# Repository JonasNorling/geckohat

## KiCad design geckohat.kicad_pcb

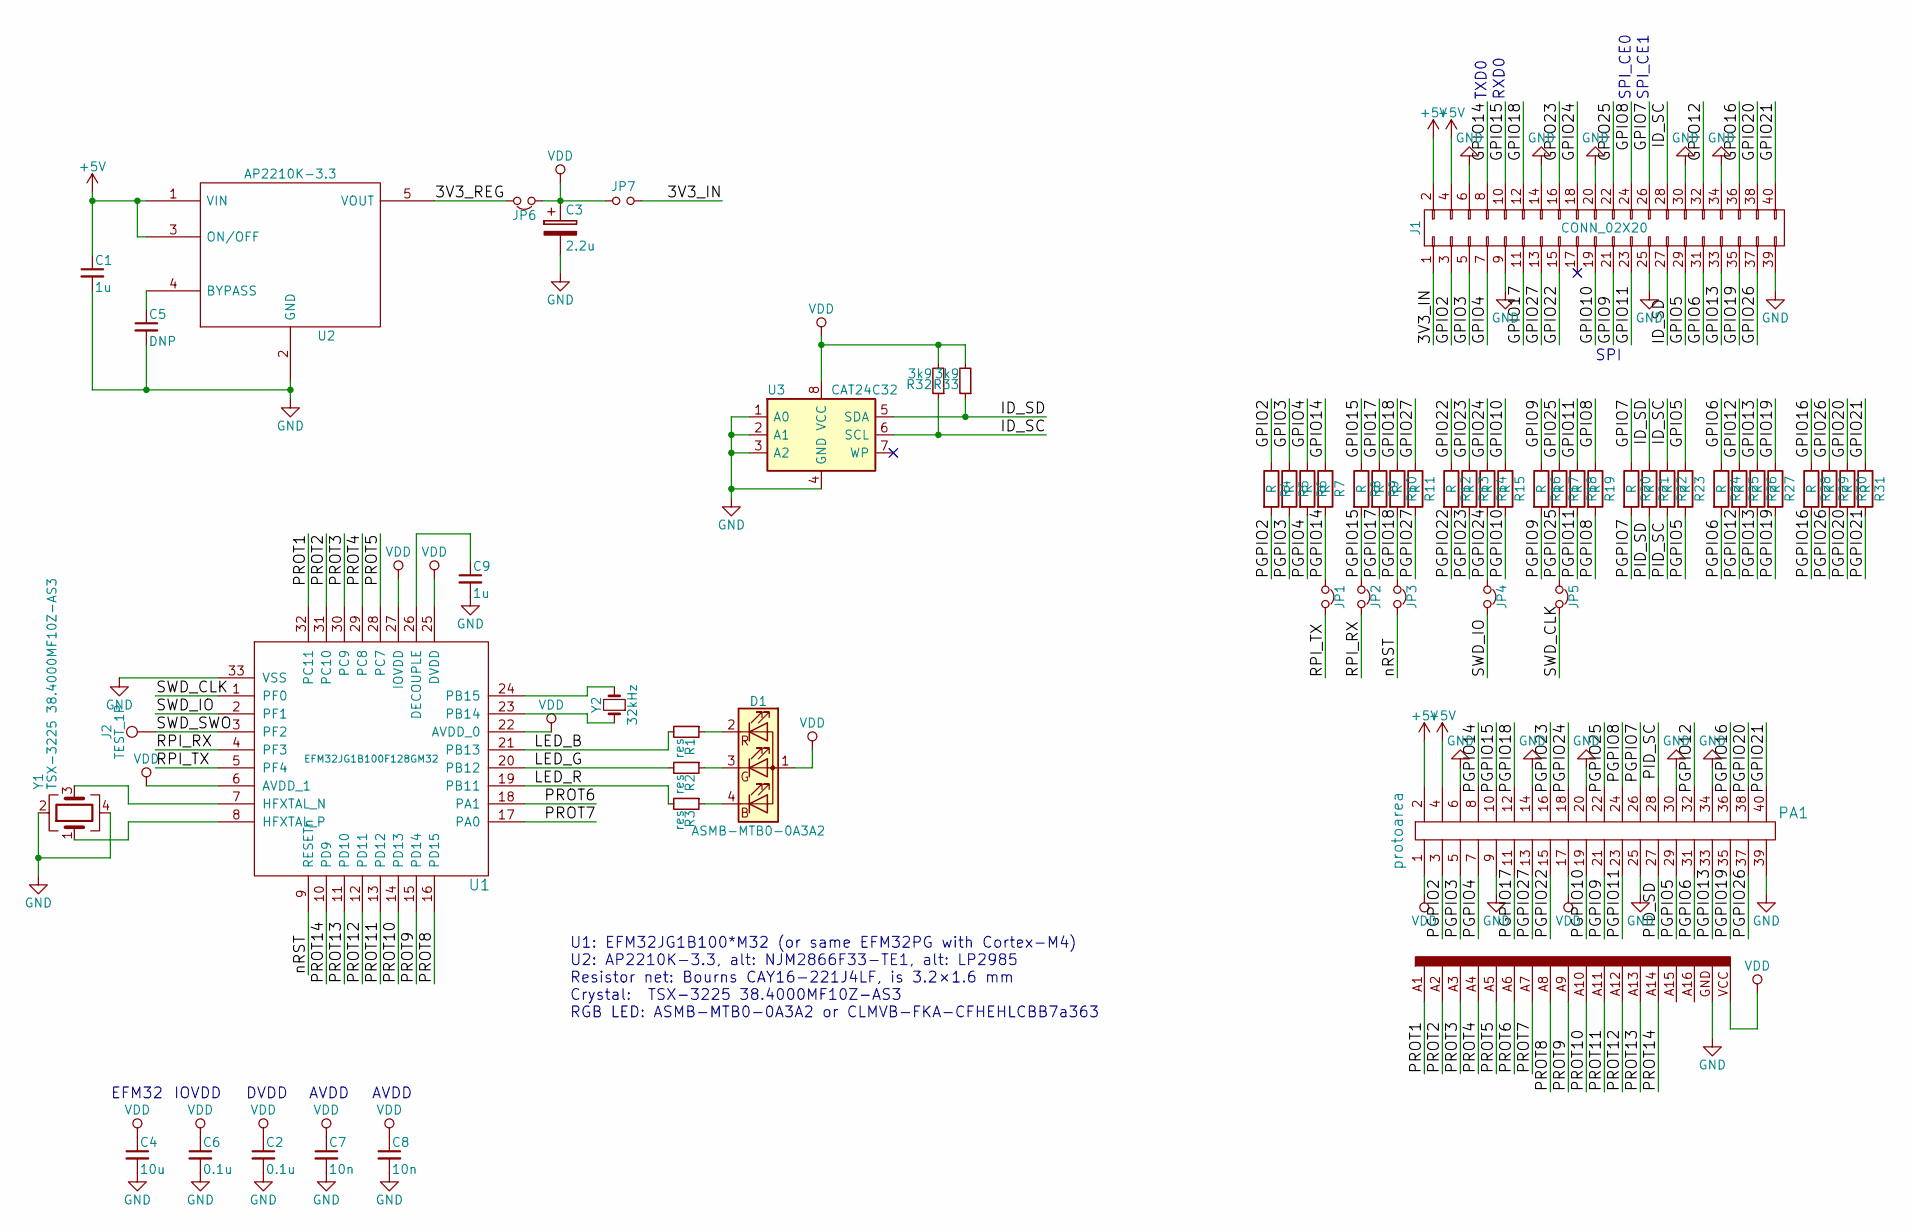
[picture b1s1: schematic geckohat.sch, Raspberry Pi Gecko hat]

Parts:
C1, C9: 1u; C_0603_1608Metric_Pad0.84x1.00mm_HandSolder
C2, C6: 0.1u; C_0603_1608Metric_Pad0.84x1.00mm_HandSolder
C3: 2.2u; C_0603_1608Metric_Pad0.84x1.00mm_HandSolder
C4: 10u; C_1206_3216Metric_Pad1.24x1.80mm_HandSolder
C5: DNP; C_0603_1608Metric_Pad0.84x1.00mm_HandSolder
C7, C8: 10n; C_0603_1608Metric_Pad0.84x1.00mm_HandSolder
D1: ASMB-MTB0-0A3A2; LED_Avago_PLCC4_3.2x2.8mm_CW
J1: CONN_02X20; Pin_Header_Straight_2x20_Pitch2.54mm
J2: TEST_1P; SolderWirePad_single_1mmDrill
JP1, JP2, JP3, JP4, JP5, JP6: tie; tie_0603
JP7: Jumper_NO_Small; tie_0603_open
PA1: protoarea
R1, R2, R3: res; R_0603_1608Metric_Pad0.84x1.00mm_HandSolder
R4, R5, R6, R7, R8, R9, R10, R11, R12, R13, R14, R15, R16, R17, R18, R19, R20, R21, R22, R23, R24, R25, R26, R27, R28, R29, R30, R31: R; R_0603_1608Metric_Pad0.84x1.00mm_HandSolder
R32, R33: 3k9; R_0603_1608Metric_Pad0.84x1.00mm_HandSolder
U1: EFM32JG1B100F128GM32; QFN-32-handsolder
U2: AP2210K-3.3; SOT-23-5_HandSoldering
U3: CAT24C32; SOIC-8_3.9x4.9mm_Pitch1.27mm
Y1: TSX-3225 38.4000MF10Z-AS3; Crystal_SMD_SeikoEpson_FA238-4pin_3.2x2.5mm_HandSoldering
Y2: 32kHz; Crystal_C26-LF_d2.1mm_l6.5mm_Vertical

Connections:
+5V: C1.1, J1.2, J1.4, PA1.2, PA1.4, U2.1 (VIN), U2.3 (ON/OFF)
/3V3_IN: J1.1, JP7.2
/3V3_REG: JP6.2, U2.5 (VOUT)
/GPIO2: J1.3, R4.1
/GPIO3: J1.5, R5.1
/GPIO4: J1.7, R6.1
/GPIO5: J1.29, R23.1
/GPIO6: J1.31, R24.1
/GPIO7: J1.26, R20.1
/GPIO8: J1.24, R19.1
/GPIO9: J1.21, R16.1
/GPIO10: J1.19, R15.1
/GPIO11: J1.23, R18.1
/GPIO12: J1.32, R25.1
/GPIO13: J1.33, R26.1
/GPIO14: J1.8, R7.1
/GPIO15: J1.10, R8.1
/GPIO16: J1.36, R28.1
/GPIO17: J1.11, R9.1
/GPIO18: J1.12, R10.1
/GPIO19: J1.35, R27.1
/GPIO20: J1.38, R30.1
/GPIO21: J1.40, R31.1
/GPIO22: J1.15, R12.1
/GPIO23: J1.16, R13.1
/GPIO24: J1.18, R14.1
/GPIO25: J1.22, R17.1
/GPIO26: J1.37, R29.1
/GPIO27: J1.13, R11.1
/ID_SC: J1.28, R22.1, R32.1, U3.6 (SCL)
/ID_SD: J1.27, R21.1, R33.1, U3.5 (SDA)
/LED_B: R1.2, U1.21 (PB13)
/LED_G: R2.2, U1.20 (PB12)
/LED_R: R3.2, U1.19 (PB11)
/PGPIO2: PA1.3, R4.2
/PGPIO3: PA1.5, R5.2
/PGPIO4: PA1.7, R6.2
/PGPIO5: PA1.29, R23.2
/PGPIO6: PA1.31, R24.2
/PGPIO7: PA1.26, R20.2
/PGPIO8: PA1.24, R19.2
/PGPIO9: PA1.21, R16.2
/PGPIO10: PA1.19, R15.2
/PGPIO11: PA1.23, R18.2
/PGPIO12: PA1.32, R25.2
/PGPIO13: PA1.33, R26.2
/PGPIO14: JP1.1, PA1.8, R7.2
/PGPIO15: JP2.1, PA1.10, R8.2
/PGPIO16: PA1.36, R28.2
/PGPIO17: PA1.11, R9.2
/PGPIO18: JP3.1, PA1.12, R10.2
/PGPIO19: PA1.35, R27.2
/PGPIO20: PA1.38, R30.2
/PGPIO21: PA1.40, R31.2
/PGPIO22: PA1.15, R12.2
/PGPIO23: PA1.16, R13.2
/PGPIO24: JP4.1, PA1.18, R14.2
/PGPIO25: JP5.1, PA1.22, R17.2
/PGPIO26: PA1.37, R29.2
/PGPIO27: PA1.13, R11.2
/PID_SC: PA1.28, R22.2
/PID_SD: PA1.27, R21.2
/PROT1: PA1.A1, U1.32 (PC11)
/PROT2: PA1.A2, U1.31 (PC10)
/PROT3: PA1.A3, U1.30 (PC9)
/PROT4: PA1.A4, U1.29 (PC8)
/PROT5: PA1.A5, U1.28 (PC7)
/PROT6: PA1.A6, U1.18 (PA1)
/PROT7: PA1.A7, U1.17 (PA0)
/PROT8: PA1.A8, U1.16 (PD15)
/PROT9: PA1.A9, U1.15 (PD14)
/PROT10: PA1.A10, U1.14 (PD13)
/PROT11: PA1.A11, U1.13 (PD12)
/PROT12: PA1.A12, U1.12 (PD11)
/PROT13: PA1.A13, U1.11 (PD10)
/PROT14: PA1.A14, U1.10 (PD9)
/RPI_RX: JP2.2, U1.4 (PF3)
/RPI_TX: JP1.2, U1.5 (PF4)
/SWD_CLK: JP5.2, U1.1 (PF0)
/SWD_IO: JP4.2, U1.2 (PF1)
/SWD_SWO: J2.1, U1.3 (PF2)
/nRST: JP3.2, U1.9 (RESETn)
GND: C1.2, C2.2, C3.2, C4.2, C5.2, C6.2, C7.2, C8.2, C9.2, J1.6, J1.9, J1.14, J1.20, J1.25, J1.30, J1.34, J1.39, PA1.6, PA1.9, PA1.14, PA1.20, PA1.25, PA1.30, PA1.34, PA1.39, PA1.GND, U1.33 (VSS), U2.2 (GND), U3.1 (A0), U3.2 (A1), U3.3 (A2), U3.4 (GND), Y1.2, Y1.4; also elsewhere on the board
unnamed: C5.1, U2.4 (BYPASS)
unnamed: C9.1, U1.26 (DECOUPLE)
unnamed: D1.2 (RK), R1.1
unnamed: D1.3 (GK), R2.1
unnamed: D1.4 (BK), R3.1
unnamed: U1.7 (HFXTAL_N), Y1.3
unnamed: U1.8 (HFXTAL_P), Y1.1
unnamed: U1.23 (PB14), Y2.1
unnamed: U1.24 (PB15), Y2.2
VDD: C2.1, C3.1, C4.1, C6.1, C7.1, C8.1, D1.1 (A), JP6.1, JP7.1, PA1.1, PA1.17, PA1.VCC, R32.2, R33.2, U1.6 (AVDD_1), U1.22 (AVDD_0), U1.25 (DVDD), U1.27 (IOVDD), U3.8 (VCC); also elsewhere on the board

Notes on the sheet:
U1: EFM32JG1B100*M32 (or same EFM32PG with Cortex-M4) U2: AP2210K-3.3, alt: NJM2866F33-TE1, alt: LP2985 Resistor net: Bourns CAY16-221J4LF, is 3.2×1.6 mm Crystal: TSX-3225 38.4000MF10Z-AS3 RGB LED: ASMB-MTB0-0A3A2 or CLMVB-FKA-CFHEHLCBB7a363
DVDD
IOVDD
EFM32
AVDD
TXD0
RXD0
SPI
SPI_CE0
SPI_CE1

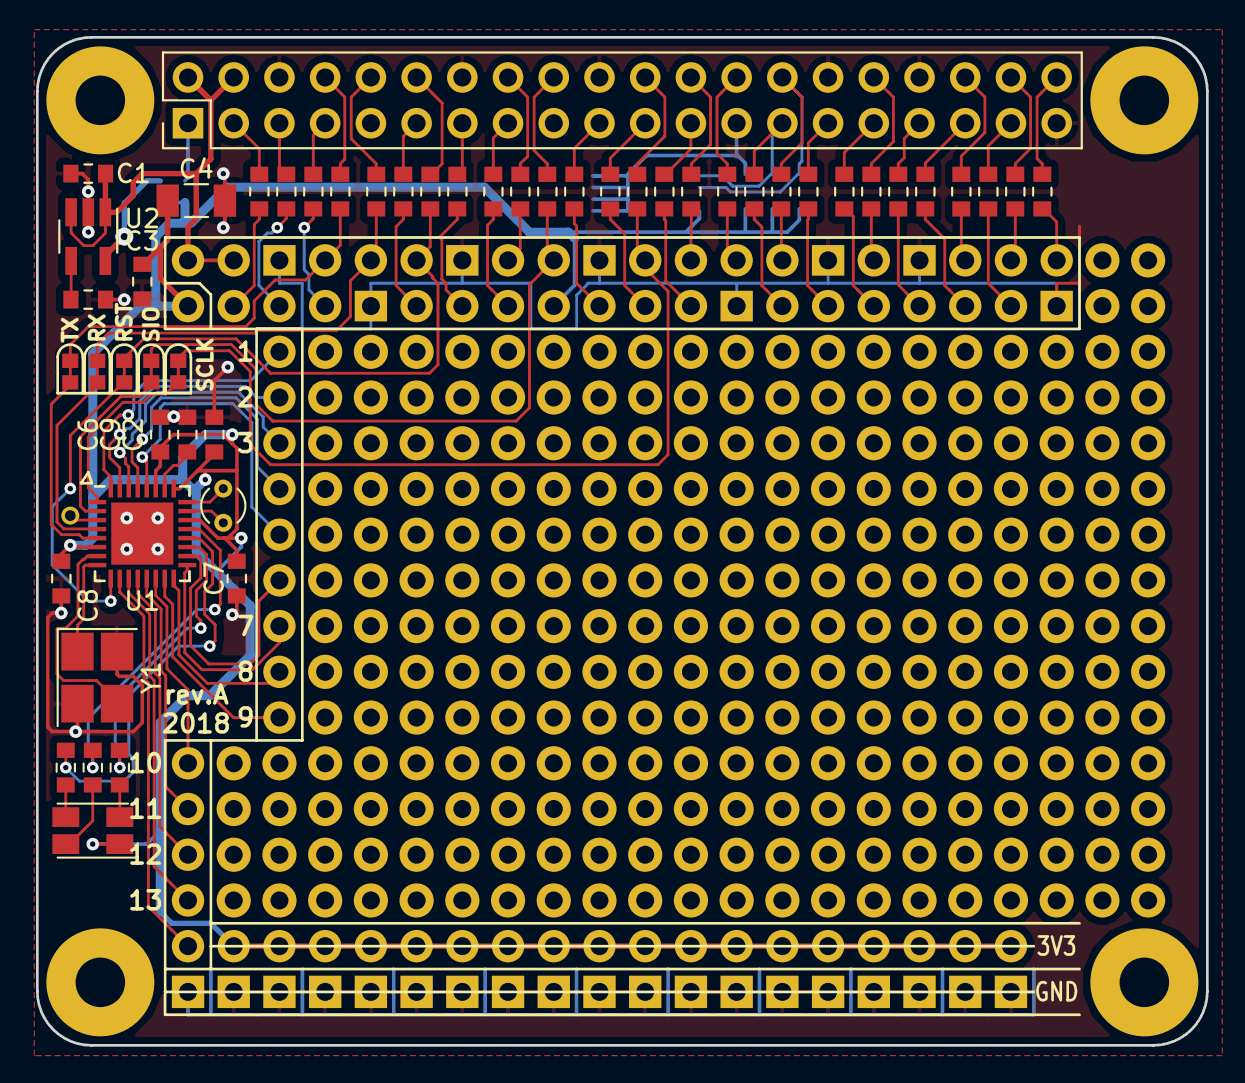
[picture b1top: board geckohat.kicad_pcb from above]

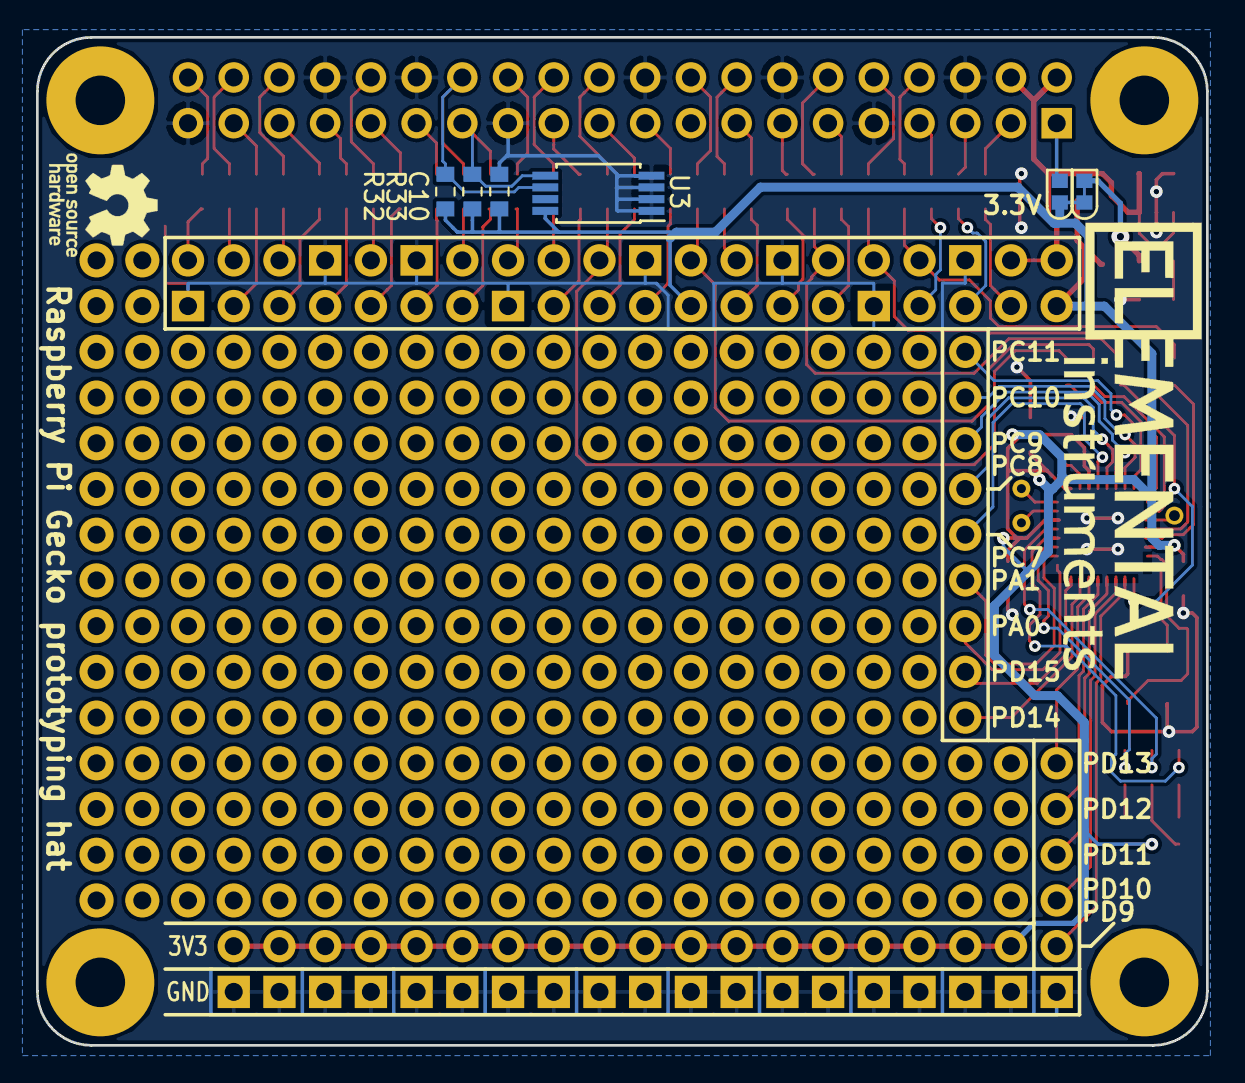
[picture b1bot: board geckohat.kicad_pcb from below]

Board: 2 copper layers, 65.0 x 56.0 mm, 59 parts (6 on the bottom side), 93 nets.

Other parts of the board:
C10: 0.1u; C_0603_1608Metric_Pad0.84x1.00mm_HandSolder

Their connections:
GND: C10.2; also elsewhere on the board
VDD: C10.1; also elsewhere on the board

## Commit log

2017-08-02 Starting...
2017-08-04 DRC fixes and stuff
2017-08-04 Net ties
2017-08-12 Set metadata, add fixme entries
2017-08-12 Elemental library
2017-08-12 Small experimental test board
2017-08-12 Get rid of grounded copper around holes
2018-02-25 Unknown changes that were lying around
2018-03-10 Add symbol cache file
2018-03-10 Work on board: fix header rotation, LED, use discreet resistors
2018-03-10 Replace a couple of cap footprints
2018-03-10 Fix silkscreen
2018-03-10 Fix 3D pin header
2018-03-11 Silkscreen updates
2018-03-11 Specify part numbers
2018-03-11 Fix pinout on proto area
2018-03-11 Silk work
2018-03-12 More silk work
2018-03-12 Improve ground fill a bit
2018-03-13 Change to TSSOP EEPROM, so it fits
2018-03-13 Gerber settings
2018-03-13 Update to 0.3mm vias, for Seeed Studio
2018-03-13 Gerbers
